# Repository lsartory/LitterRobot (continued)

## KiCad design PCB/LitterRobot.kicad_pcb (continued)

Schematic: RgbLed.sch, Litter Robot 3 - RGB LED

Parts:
D8: SMLVN6RGB1U; ROHM_SMLVN6; Part_number SMLVN6RGB1U1
Q16, Q17, Q18: BC817; SOT-23; Part_number BC817-25,215
R52: 178R; R_0603_1608Metric; Part_number CR0603-FX-1780ELF
R53, R54: 221R; R_0603_1608Metric; Part_number CR0603-FX-2210ELF

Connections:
+7V: D8.1 (BA), D8.2 (RA), D8.3 (GA); also elsewhere on the board
/Control panel/Left_LED_B: Q18.1 (B); also elsewhere on the board
/Control panel/Left_LED_G: Q16.1 (B); also elsewhere on the board
/Control panel/Left_LED_R: Q17.1 (B); also elsewhere on the board
GND: R52.2, R53.2, R54.2; also elsewhere on the board
unnamed: D8.4 (GK), Q16.3 (C)
unnamed: D8.5 (RK), Q17.3 (C)
unnamed: D8.6 (BK), Q18.3 (C)
unnamed: Q16.2 (E), R52.1
unnamed: Q17.2 (E), R53.1
unnamed: Q18.2 (E), R54.1

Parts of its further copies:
D4, D5, D6, D7, D9, D10: SMLVN6RGB1U; ROHM_SMLVN6; Part_number SMLVN6RGB1U1
Q4, Q5, Q6, Q7, Q8, Q9, Q10, Q11, Q12, Q13, Q14, Q15, Q19, Q20, Q21, Q22, Q23, Q24: BC817; SOT-23; Part_number BC817-25,215
R40, R43, R46, R49, R55, R58: 178R; R_0603_1608Metric; Part_number CR0603-FX-1780ELF
R41, R42, R44, R45, R47, R48, R50, R51, R56, R57, R59, R60: 221R; R_0603_1608Metric; Part_number CR0603-FX-2210ELF

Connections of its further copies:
+7V: D4.1 (BA), D4.2 (RA), D4.3 (GA), D5.1 (BA), D5.2 (RA), D5.3 (GA), D6.1 (BA), D6.2 (RA), D6.3 (GA), D7.1 (BA), D7.2 (RA), D7.3 (GA), D9.1 (BA), D9.2 (RA), D9.3 (GA), D10.1 (BA), D10.2 (RA), D10.3 (GA); also elsewhere on the board
/Control panel/Center_LED_B: Q21.1 (B); also elsewhere on the board
/Control panel/Center_LED_G: Q19.1 (B); also elsewhere on the board
/Control panel/Center_LED_R: Q20.1 (B); also elsewhere on the board
/Control panel/Cycle_LED_B: Q9.1 (B); also elsewhere on the board
/Control panel/Cycle_LED_G: Q7.1 (B); also elsewhere on the board
/Control panel/Cycle_LED_R: Q8.1 (B); also elsewhere on the board
/Control panel/Empty_LED_B: Q12.1 (B); also elsewhere on the board
/Control panel/Empty_LED_G: Q10.1 (B); also elsewhere on the board
/Control panel/Empty_LED_R: Q11.1 (B); also elsewhere on the board
/Control panel/Power_LED_B: Q6.1 (B); also elsewhere on the board
/Control panel/Power_LED_G: Q4.1 (B); also elsewhere on the board
/Control panel/Power_LED_R: Q5.1 (B); also elsewhere on the board
/Control panel/Reset_LED_B: Q15.1 (B); also elsewhere on the board
/Control panel/Reset_LED_G: Q13.1 (B); also elsewhere on the board
/Control panel/Reset_LED_R: Q14.1 (B); also elsewhere on the board
/Control panel/Right_LED_B: Q24.1 (B); also elsewhere on the board
/Control panel/Right_LED_G: Q22.1 (B); also elsewhere on the board
/Control panel/Right_LED_R: Q23.1 (B); also elsewhere on the board
GND: R40.2, R41.2, R42.2, R43.2, R44.2, R45.2, R46.2, R47.2, R48.2, R49.2, R50.2, R51.2, R55.2, R56.2, R57.2, R58.2, R59.2, R60.2; also elsewhere on the board
unnamed: D4.4 (GK), Q4.3 (C)
unnamed: D4.5 (RK), Q5.3 (C)
unnamed: D4.6 (BK), Q6.3 (C)
unnamed: D5.4 (GK), Q7.3 (C)
unnamed: D5.5 (RK), Q8.3 (C)
unnamed: D5.6 (BK), Q9.3 (C)
unnamed: D6.4 (GK), Q10.3 (C)
unnamed: D6.5 (RK), Q11.3 (C)
unnamed: D6.6 (BK), Q12.3 (C)
unnamed: D7.4 (GK), Q13.3 (C)
unnamed: D7.5 (RK), Q14.3 (C)
unnamed: D7.6 (BK), Q15.3 (C)
unnamed: D9.4 (GK), Q19.3 (C)
unnamed: D9.5 (RK), Q20.3 (C)
unnamed: D9.6 (BK), Q21.3 (C)
unnamed: D10.4 (GK), Q22.3 (C)
unnamed: D10.5 (RK), Q23.3 (C)
unnamed: D10.6 (BK), Q24.3 (C)
unnamed: Q4.2 (E), R40.1
unnamed: Q5.2 (E), R41.1
unnamed: Q6.2 (E), R42.1
unnamed: Q7.2 (E), R43.1
unnamed: Q8.2 (E), R44.1
unnamed: Q9.2 (E), R45.1
unnamed: Q10.2 (E), R46.1
unnamed: Q11.2 (E), R47.1
unnamed: Q12.2 (E), R48.1
unnamed: Q13.2 (E), R49.1
unnamed: Q14.2 (E), R50.1
unnamed: Q15.2 (E), R51.1
unnamed: Q19.2 (E), R55.1
unnamed: Q20.2 (E), R56.1
unnamed: Q21.2 (E), R57.1
unnamed: Q22.2 (E), R58.1
unnamed: Q23.2 (E), R59.1
unnamed: Q24.2 (E), R60.1

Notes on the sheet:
For white light, the following currents are required: Ired = 12 mA Igreen = 15 mA Iblue = 12 mA The resistors were calculated for +3.3 V signals (Vbe of the transistors is approximated at 0.65 V)

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
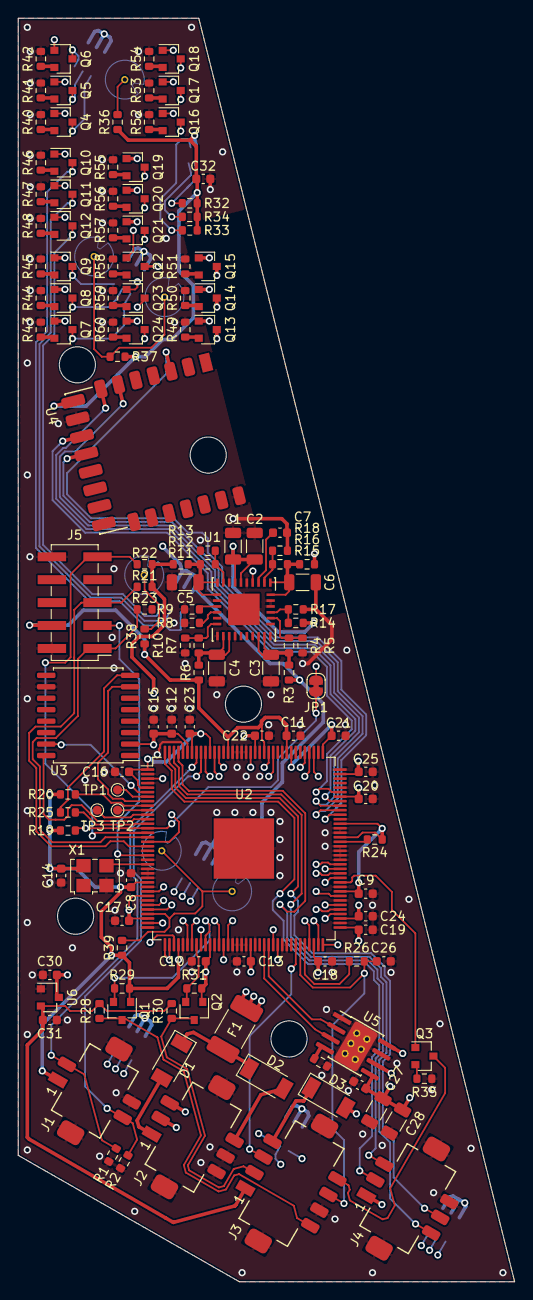
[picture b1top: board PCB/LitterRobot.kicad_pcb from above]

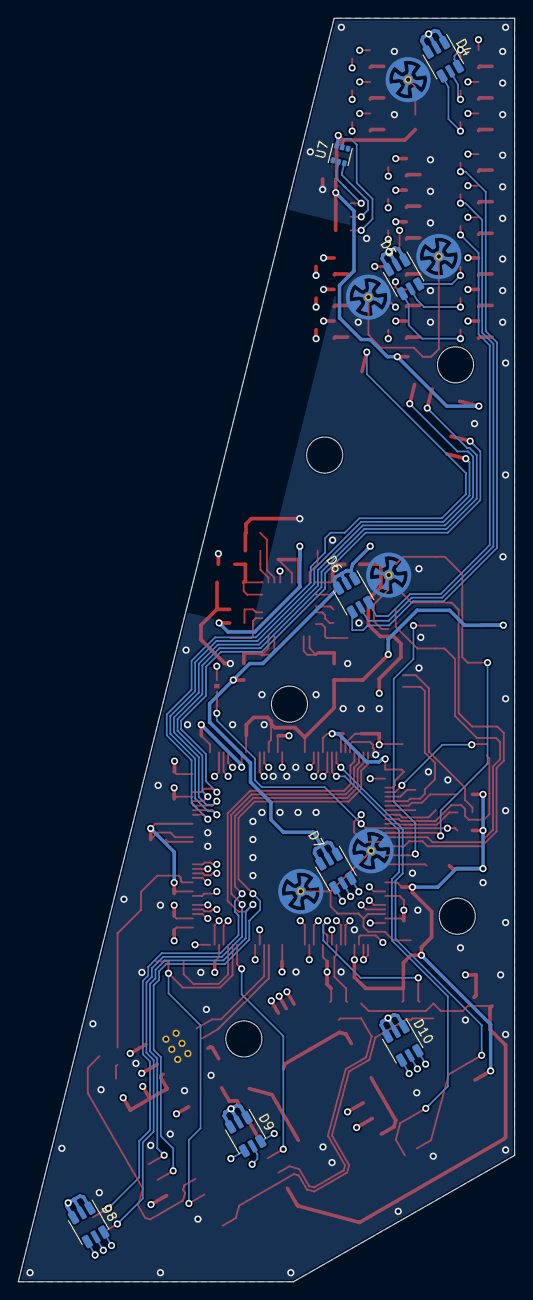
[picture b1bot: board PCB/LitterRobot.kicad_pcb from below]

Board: 4 copper layers, 55.0 x 140.0 mm, 155 parts (19 on the bottom side), 136 nets.

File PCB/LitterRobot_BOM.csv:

Part_number,Quantity,Reference,Value
C3216X5R1V226M160AC,6,C1 C2 C3 C4 C5 C6,22µF
C3216X5R1E476M160AC,2,C27 C28,47µF
C1608X5R1H105K080AB,3,C7 C30 C31,1µF
C1608X5R1H104K080AA,21,C8 C9 C10 C11 C12 C13 C14 C15 C16 C17 C18 C19 C20 C21 C22 C23 C24 C25 C26 C29 C32,100nF
VS-2EYH02HM3/H,3,D1 D2 D3,VS-2EYH02HM3/H
SMLVN6RGB1U1,7,D4 D5 D6 D7 D8 D9 D10,SMLVN6RGB1U
0ZCG0110BF2B,1,F1,1.1A
DF11C-4DP-2V(57),1,J1,DF11C-4DP-2V(57)
DF11C-6DP-2V(57),2,J2 J4,DF11C-6DP-2V(57)
DF11C-8DP-2V(57),1,J3,DF11C-8DP-2V(57)
TSM-105-01-S-DV,1,J5,TSM-105-01-S-DV
"BSS138P,215",2,Q1 Q2,BSS138
"BC817-25,215",22,Q3 Q4 Q5 Q6 Q7 Q8 Q9 Q10 Q11 Q12 Q13 Q14 Q15 Q16 Q17 Q18 Q19 Q20 Q21 Q22 Q23 Q24,BC817
CR0603-FX-1002ELF,19,R1 R2 R8 R9 R14 R19 R20 R21 R22 R24 R26 R28 R29 R30 R31 R36 R37 R38 R39,10k
CR0603-FX-2551ELF,1,R10,2.55k
CR0603-FX-9311ELF,1,R12,9.31k
CR0603-FX-2941ELF,1,R13,2.94k
CR0603-FX-3301ELF,6,R16 R17 R18 R32 R33 R34,3.3k
CR0603-FX-1001ELF,1,R23,1k
CR0603-FX-24R9ELF,1,R25,24.9
CR0603-FX-2802ELF,1,R27,28k
CR0603-J/-000ELF,4,R3 R6 R11 R15,0R
CR0603-FX-1780ELF,8,R35 R40 R43 R46 R49 R52 R55 R58,178R
CR0603-FX-2002ELF,1,R4,20k
CR0603-FX-2210ELF,14,R41 R42 R44 R45 R47 R48 R50 R51 R53 R54 R56 R57 R59 R60,221R
CR0603-FX-1871ELF,1,R5,1.87k
CR0603-FX-1152ELF,1,R7,11.5k
MPM54304GMN-0001,1,U1,MPM54304GMN-0001
10CL016YE144C8G,1,U2,10CL016YE144C8G
S25FL128SAGMFI000,1,U3,S25FL128SAGMFI000
113990637,1,U4,EMB1061
DRV8871DDARQ1,1,U5,DRV8871DDA
MCP1700T-5002E/TT,1,U6,MCP1700T-5002E/TT
VEML6035,1,U7,VEML6035
X1G0044510011,1,X1,X1G0044510011

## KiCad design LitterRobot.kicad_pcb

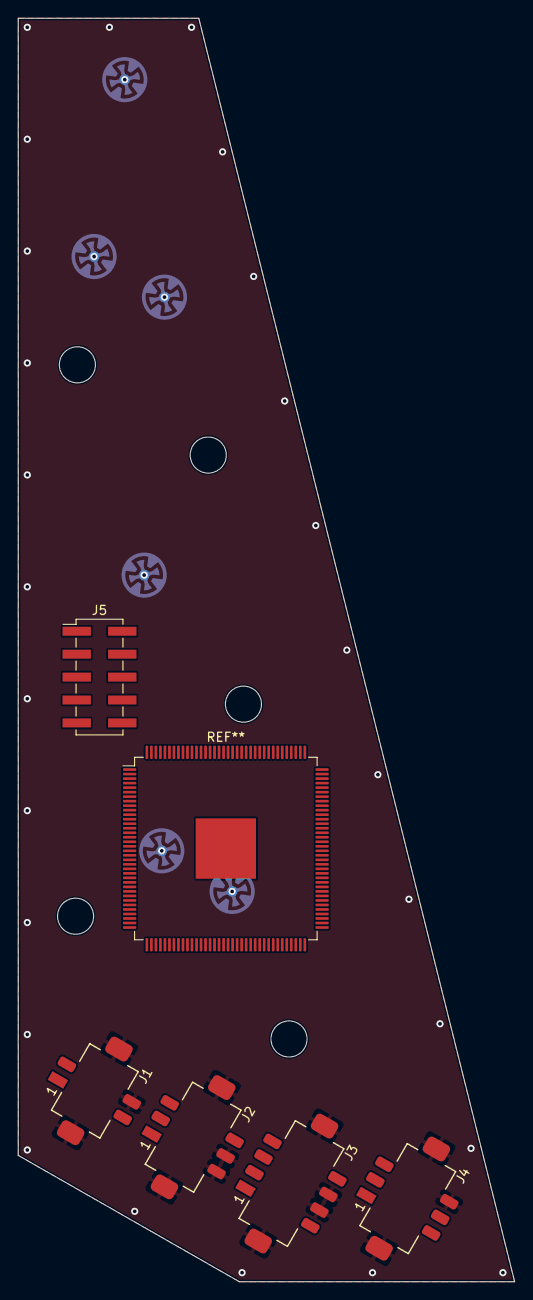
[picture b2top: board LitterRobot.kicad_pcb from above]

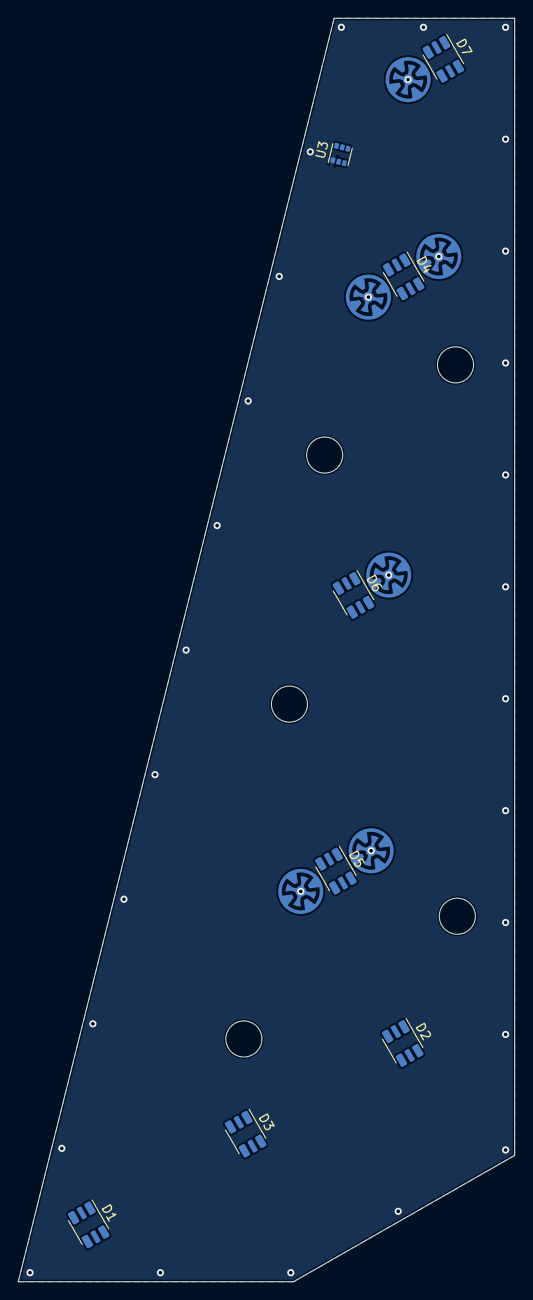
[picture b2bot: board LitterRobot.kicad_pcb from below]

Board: 4 copper layers, 55.0 x 140.0 mm, 24 parts (14 on the bottom side), 5 nets, no tracks yet.

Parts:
D1, D2, D3, D4, D5, D6, D7: SMLVN6RGB1U; ROHM_SMLVN6
H1, H2, H3, H4, H5: MountingHole; MountingHole_4mm
J1: DF11C-4DP-2V(57); Hirose_DF11C-4DP-2V(57)
J2, J4: DF11C-6DP-2V(57); Hirose_DF11C-6DP-2V(57)
J3: DF11C-8DP-2V(57); Hirose_DF11C-8DP-2V(57)
J5: Conn_02x05_Odd_Even; PinHeader_2x05_P2.54mm_Vertical_SMD
SW1, SW2, SW3, SW4, SW5, SW6: PCB_Push_Button; PCB_Push_Button_5mm_0.4mm
U3: VEML6035; Vishay_VEML6035

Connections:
+3V3: J1.1, SW1.1, SW2.1, SW3.1, SW4.1, SW5.1, SW6.1, U3.6
+7V: D1.1, D1.2, D1.3, D2.1, D2.2, D2.3, D3.1, D3.2, D3.3, D4.1, D4.2, D4.3, D5.1, D5.2, D5.3, D6.1, D6.2, D6.3, D7.1, D7.2, D7.3
/Cycle_button: SW3.2, SW4.2
/Reset_button: SW5.2, SW6.2
GND: J1.4, J1.MP, J2.2, J2.4, J2.MP, J3.4, J3.6, J3.MP, J4.6, J4.MP, U3.1

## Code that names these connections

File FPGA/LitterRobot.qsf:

set_global_assignment -name TOP_LEVEL_ENTITY LitterRobot
set_global_assignment -name ORIGINAL_QUARTUS_VERSION 20.1.1
set_global_assignment -name PROJECT_CREATION_TIME_DATE "17:55:34  MARCH 27, 2021"
set_global_assignment -name LAST_QUARTUS_VERSION "20.1.1 Lite Edition"
set_global_assignment -name PROJECT_OUTPUT_DIRECTORY output_files
set_global_assignment -name PROJECT_IP_REGENERATION_POLICY ALWAYS_REGENERATE_IP
set_global_assignment -name SAVE_DISK_SPACE OFF
set_global_assignment -name SMART_RECOMPILE ON
set_global_assignment -name TIMING_ANALYZER_MULTICORNER_ANALYSIS ON
set_global_assignment -name FLOW_ENABLE_IO_ASSIGNMENT_ANALYSIS ON
set_global_assignment -name NUM_PARALLEL_PROCESSORS 4

set_global_assignment -name FAMILY "Cyclone 10 LP"
set_global_assignment -name DEVICE 10CL016YE144C8G
set_global_assignment -name DEVICE_MIGRATION_LIST "10CL016YE144C8G,10CL006YE144C8G,10CL010YE144C8G,10CL025YE144C8G"

set_global_assignment -name USE_CONFIGURATION_DEVICE ON
set_global_assignment -name CYCLONEIII_CONFIGURATION_DEVICE S25FL128
set_global_assignment -name CONFIGURATION_VCCIO_LEVEL 3.3V
set_global_assignment -name GENERATE_RBF_FILE ON

set_global_assignment -name NOMINAL_CORE_SUPPLY_VOLTAGE 1.2V
set_global_assignment -name STRATIX_DEVICE_IO_STANDARD "3.3-V LVTTL"
set_global_assignment -name MIN_CORE_JUNCTION_TEMP 0
set_global_assignment -name MAX_CORE_JUNCTION_TEMP 85
set_global_assignment -name POWER_USE_DEVICE_CHARACTERISTICS MAXIMUM
set_global_assignment -name POWER_PRESET_COOLING_SOLUTION "NO HEAT SINK WITH STILL AIR"
set_global_assignment -name POWER_BOARD_THERMAL_MODEL "NONE (CONSERVATIVE)"

set_global_assignment -name RESERVE_ALL_UNUSED_PINS_WEAK_PULLUP "AS INPUT TRI-STATED"
set_global_assignment -name ENABLE_BOOT_SEL_PIN OFF
set_global_assignment -name ENABLE_CONFIGURATION_PINS OFF
set_global_assignment -name ENABLE_OCT_DONE OFF

set_global_assignment -name OUTPUT_IO_TIMING_NEAR_END_VMEAS "HALF VCCIO" -rise
set_global_assignment -name OUTPUT_IO_TIMING_NEAR_END_VMEAS "HALF VCCIO" -fall
set_global_assignment -name OUTPUT_IO_TIMING_FAR_END_VMEAS "HALF SIGNAL SWING" -rise
set_global_assignment -name OUTPUT_IO_TIMING_FAR_END_VMEAS "HALF SIGNAL SWING" -fall

set_global_assignment -name CYCLONEII_RESERVE_NCEO_AFTER_CONFIGURATION "USE AS REGULAR IO"
set_global_assignment -name CRC_ERROR_CHECKING OFF
set_global_assignment -name CRC_ERROR_OPEN_DRAIN OFF

set_location_assignment PIN_22 -to CLK_20MHz
set_location_assignment PIN_98 -to BLUETOOTH_RESETn
set_location_assignment PIN_99 -to BLUETOOTH_TX
set_location_assignment PIN_103 -to BLUETOOTH_RX
set_location_assignment PIN_100 -to BLUETOOTH_RTSn
set_location_assignment PIN_101 -to BLUETOOTH_CTSn
set_location_assignment PIN_67 -to WEIGHT
set_location_assignment PIN_68 -to WEIGHT_REF
set_location_assignment PIN_66 -to WEIGHT_FSR
set_location_assignment PIN_59 -to MOTOR_PWM[1]
set_location_assignment PIN_60 -to MOTOR_PWM[2]
set_location_assignment PIN_46 -to HALL_SENSOR_L
set_location_assignment PIN_44 -to HALL_SENSOR_R
set_location_assignment PIN_136 -to DFI[1]
set_location_assignment PIN_137 -to DFI[2]
set_location_assignment PIN_111 -to LIGHT_SENSOR_SDA
set_location_assignment PIN_113 -to LIGHT_SENSOR_SCL
set_location_assignment PIN_112 -to LIGHT_SENSOR_INT
set_location_assignment PIN_83 -to DOME_LED
set_location_assignment PIN_28 -to POWER_BUTTON
set_location_assignment PIN_31 -to CYCLE_BUTTON
set_location_assignment PIN_32 -to EMPTY_BUTTON
set_location_assignment PIN_33 -to RESET_BUTTON
set_location_assignment PIN_76 -to POWER_LED_R
set_location_assignment PIN_72 -to POWER_LED_G
set_location_assignment PIN_71 -to POWER_LED_B
set_location_assignment PIN_39 -to CYCLE_LED_R
set_location_assignment PIN_43 -to CYCLE_LED_G
set_location_assignment PIN_42 -to CYCLE_LED_B
set_location_assignment PIN_50 -to EMPTY_LED_R
set_location_assignment PIN_51 -to EMPTY_LED_G
set_location_assignment PIN_49 -to EMPTY_LED_B
set_location_assignment PIN_121 -to RESET_LED_R
set_location_assignment PIN_120 -to RESET_LED_G
set_location_assignment PIN_125 -to RESET_LED_B
set_location_assignment PIN_133 -to LEFT_LED_R
set_location_assignment PIN_132 -to LEFT_LED_G
set_location_assignment PIN_135 -to LEFT_LED_B
set_location_assignment PIN_87 -to CENTER_LED_R
set_location_assignment PIN_86 -to CENTER_LED_G
set_location_assignment PIN_85 -to CENTER_LED_B
set_location_assignment PIN_77 -to RIGHT_LED_R
set_location_assignment PIN_69 -to RIGHT_LED_G
set_location_assignment PIN_80 -to RIGHT_LED_B

set_instance_assignment -name CURRENT_STRENGTH_NEW "MAXIMUM CURRENT" -to *_LED_*
set_instance_assignment -name CURRENT_STRENGTH_NEW "MAXIMUM CURRENT" -to BLUETOOTH_*
set_instance_assignment -name CURRENT_STRENGTH_NEW "MAXIMUM CURRENT" -to DFI*
set_instance_assignment -name CURRENT_STRENGTH_NEW "MAXIMUM CURRENT" -to DOME_LED
set_instance_assignment -name CURRENT_STRENGTH_NEW "MAXIMUM CURRENT" -to LIGHT_SENSOR_*
set_instance_assignment -name CURRENT_STRENGTH_NEW "MAXIMUM CURRENT" -to MOTOR_PWM*
set_instance_assignment -name CURRENT_STRENGTH_NEW "MAXIMUM CURRENT" -to WEIGHT*

set_global_assignment -name SDC_FILE LitterRobot.sdc
set_global_assignment -name VHDL_FILE AmbientLightSensor.vhd
set_global_assignment -name VHDL_FILE ClockScaler.vhd
set_global_assignment -name VHDL_FILE CycleProcess.vhd
set_global_assignment -name VHDL_FILE I2cController.vhd
set_global_assignment -name VHDL_FILE LedController.vhd
set_global_assignment -name VHDL_FILE LedModulator.vhd
set_global_assignment -name VHDL_FILE LitterRobot.vhd
set_global_assignment -name VHDL_FILE PinchSensor.vhd
set_global_assignment -name VHDL_FILE PulseDensityModulator.vhd
set_global_assignment -name VHDL_FILE WeightSensor.vhd

set_global_assignment -name PARTITION_NETLIST_TYPE SOURCE -section_id Top
set_global_assignment -name PARTITION_FITTER_PRESERVATION_LEVEL PLACEMENT_AND_ROUTING -section_id Top
set_global_assignment -name PARTITION_COLOR 16764057 -section_id Top
set_instance_assignment -name PARTITION_HIERARCHY root_partition -to | -section_id Top

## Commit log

2021-02-28 Add more Hirose connectors 3D models
2021-02-28 Added Hirose footprints
2021-02-28 Add RGB LEDs to the schematic
2021-03-02 Add an extension connector
2021-03-02 Add placeholder sheets for functions to be implemented
2021-03-07 Add the power supply and motor driver ICs
2021-03-07 Add the MPM54304 footprint
2021-03-07 Add the board outline
2021-03-11 Add / improve 3D models
2021-03-13 Add the push buttons and mounting holes
2021-03-14 Place the main components on the PCB
2021-03-16 Add TODO notes
2021-03-20 Add a footprint for Bel Fuse 0ZCG PTCs
2021-03-20 Add fuse and more inter-page signals
2021-03-20 Add an ambient light sensor
2021-03-20 Add the missing light sensor files
2021-03-20 Add the FPGA footprint
2021-03-27 Add support components for the FPGA
    - Configuration EEPROM
    - 20 MHz oscillator
    - JTAG debug port connector
2021-03-27 Update the TODO lists
2021-03-27 Initial commit of the Quartus project
2021-03-28 Add the FPGA symbol
2021-03-28 Connect the FPGA configuration signals
2021-03-28 Add missing capacitor datasheets
2021-03-28 Cleaned up the schematics
2021-03-28 Plot the schematic as PDF
2021-04-02 Improve the push buttons
2021-04-02 Add reverse polarity protection diodes
2021-04-02 Add support for the weight sensor
2021-04-03 Add support for the hall sensors and dome LED
2021-04-05 Reduce the weight sensor capacitor value
2021-04-05 Fix the oscillator footprint
2021-04-05 Re-annotate all components
2021-04-05 Add vias to the PCB push button footprints
2021-04-05 Add a 3D model for the oscillator
2021-04-05 Change the higher value capacitors to 1206
2021-04-05 Add a 3D model for the SlimSMAW diodes
2021-04-05 Place all the components on the board
2021-04-05 Update the schematics PDF
2021-04-05 Adapt the DRV8871 footprint for the PCB constraints
2021-04-05 Fix the VEML6035 pad clearance
2021-04-10 Add the EMB1061 Bluetooth module
2021-04-10 Connect the Bluetooth module to the FPGA
2021-04-11 Place the Bluetooth module on the PCB
2021-04-11 Start routing the PCB
2021-04-11 Improve the PCB push button footprints
2021-05-02 Route more signals
2021-05-17 Fix invalid / missing part numbers
2021-05-24 Complete routing all signals
2021-05-24 Export BOM
2021-05-24 Add jumpers on the power supply outputs
2021-05-29 Increase via drill size to 0.45 mm
2021-06-23 Add FPGA pin assignments and a simple modulator for the LEDs
2021-06-23 Fix the positions of R4 and R5 in the silkscreen layer
2021-06-27 Add a LED controller and temporary test implementation
2021-07-05 Animate the LEDs and make them brighter when buttons are pressed
2021-07-05 Add pinch detection
2021-07-05 Add basic resistance measurement
2021-07-17 Implement the light sensor interface
2021-07-31 Dim the LEDs depending on the ambient brightness
2021-08-21 Improve the LED brightness control
2021-08-21 Implement the waste removal cycle
